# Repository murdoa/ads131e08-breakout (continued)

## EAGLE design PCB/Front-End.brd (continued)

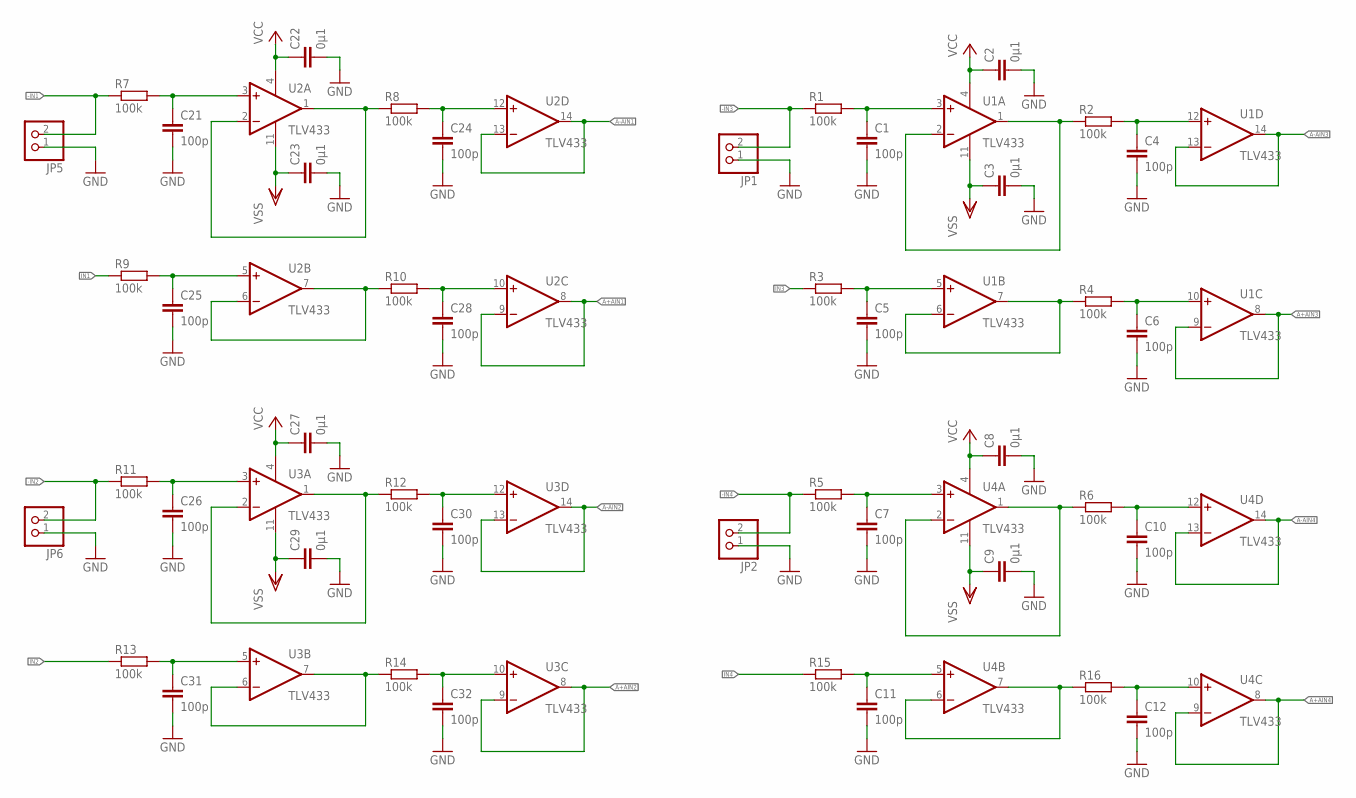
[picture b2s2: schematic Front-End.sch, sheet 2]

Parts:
C1, C4, C5, C6, C7, C10, C11, C12, C21, C24, C25, C26, C28, C30, C31, C32: 100p; C0603
C2, C3, C8, C9, C22, C23, C27, C29: 0µ1; C0603
JP1, JP2, JP5, JP6: PINHD-1X2; 1X02
R1, R2, R3, R4, R5, R6, R7, R8, R9, R10, R11, R12, R13, R14, R15, R16: 100k; R0603
U1, U2, U3, U4: TLV433; TSSOP14

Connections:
-IN1: JP5.2, R7.1
-IN2: JP6.2, R11.1
-IN3: JP1.2, R1.1
-IN4: JP2.2, R5.1
-PAS1: C21.1, R7.2, U2.3 (+IN); also elsewhere on the board
-PAS2: C26.1, R11.2, U3.3 (+IN); also elsewhere on the board
-PAS3: C1.1, R1.2, U1.3 (+IN); also elsewhere on the board
-PAS4: C7.1, R5.2, U4.3 (+IN); also elsewhere on the board
A+AIN1: U2.8 (OUT), U2.9 (-IN); also elsewhere on the board
A+AIN2: U3.8 (OUT), U3.9 (-IN); also elsewhere on the board
A+AIN3: U1.8 (OUT), U1.9 (-IN); also elsewhere on the board
A+AIN4: U4.8 (OUT), U4.9 (-IN); also elsewhere on the board
A-AIN1: U2.13 (-IN), U2.14 (OUT); also elsewhere on the board
A-AIN2: U3.13 (-IN), U3.14 (OUT); also elsewhere on the board
A-AIN3: U1.13 (-IN), U1.14 (OUT); also elsewhere on the board
A-AIN4: U4.13 (-IN), U4.14 (OUT); also elsewhere on the board
GND: C1.2, C2.2, C3.2, C4.2, C5.2, C6.2, C7.2, C8.2, C9.2, C10.2, C11.2, C12.2, C21.2, C22.2, C23.2, C24.2, C25.2, C26.2, C27.2, C28.2, C29.2, C30.2, C31.2, C32.2, JP1.1, JP2.1, JP5.1, JP6.1; also elsewhere on the board
IN1: R9.1
IN2: R13.1
IN3: R3.1
IN4: R15.1
unnamed: C4.1, R2.2, U1.12 (+IN)
unnamed: R2.1, U1.1 (OUT), U1.2 (-IN)
unnamed: C6.1, R4.2, U1.10 (+IN)
unnamed: C28.1, R10.2, U2.10 (+IN)
unnamed: C24.1, R8.2, U2.12 (+IN)
unnamed: R8.1, U2.1 (OUT), U2.2 (-IN)
unnamed: R10.1, U2.6 (-IN), U2.7 (OUT)
unnamed: R4.1, U1.6 (-IN), U1.7 (OUT)
unnamed: C30.1, R12.2, U3.12 (+IN)
unnamed: R12.1, U3.1 (OUT), U3.2 (-IN)
unnamed: C10.1, R6.2, U4.12 (+IN)
unnamed: C32.1, R14.2, U3.10 (+IN)
unnamed: R14.1, U3.6 (-IN), U3.7 (OUT)
unnamed: R6.1, U4.1 (OUT), U4.2 (-IN)
unnamed: C12.1, R16.2, U4.10 (+IN)
unnamed: R16.1, U4.6 (-IN), U4.7 (OUT)
PAS1: C5.1, C25.1, R3.2, R9.2, U1.5 (+IN), U2.5 (+IN); also elsewhere on the board
PAS2: C11.1, C31.1, R13.2, R15.2, U3.5 (+IN), U4.5 (+IN); also elsewhere on the board
VCC: C2.1, C8.1, C22.1, C27.1, U1.4 (V+), U2.4 (V+), U3.4 (V+), U4.4 (V+); also elsewhere on the board
VSS: C3.1, C9.1, C23.1, C29.1, U1.11 (V-), U2.11 (V-), U3.11 (V-), U4.11 (V-); also elsewhere on the board

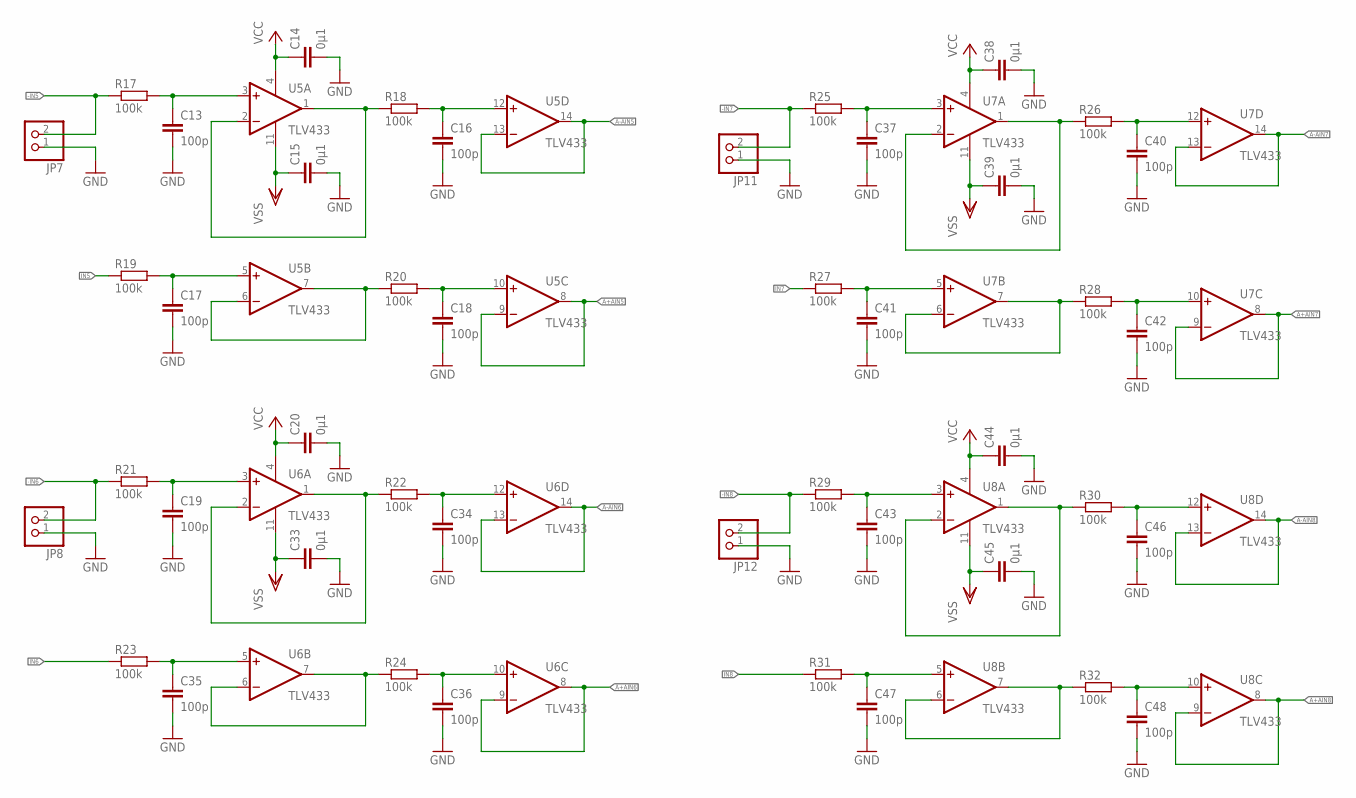
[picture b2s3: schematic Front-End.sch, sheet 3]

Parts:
C13, C16, C17, C18, C19, C34, C35, C36, C37, C40, C41, C42, C43, C46, C47, C48: 100p; C0603
C14, C15, C20, C33, C38, C39, C44, C45: 0µ1; C0603
JP7, JP8, JP11, JP12: PINHD-1X2; 1X02
R17, R18, R19, R20, R21, R22, R23, R24, R25, R26, R27, R28, R29, R30, R31, R32: 100k; R0603
U5, U6, U7, U8: TLV433; TSSOP14

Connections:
-IN5: JP7.2, R17.1
-IN6: JP8.2, R21.1
-IN7: JP11.2, R25.1
-IN8: JP12.2, R29.1
-PAS5: C13.1, R17.2, U5.3 (+IN); also elsewhere on the board
-PAS6: C19.1, R21.2, U6.3 (+IN); also elsewhere on the board
-PAS7: C37.1, R25.2, U7.3 (+IN); also elsewhere on the board
-PAS8: C43.1, R29.2, U8.3 (+IN); also elsewhere on the board
A+AIN5: U5.8 (OUT), U5.9 (-IN); also elsewhere on the board
A+AIN6: U6.8 (OUT), U6.9 (-IN); also elsewhere on the board
A+AIN7: U7.8 (OUT), U7.9 (-IN); also elsewhere on the board
A+AIN8: U8.8 (OUT), U8.9 (-IN); also elsewhere on the board
A-AIN5: U5.13 (-IN), U5.14 (OUT); also elsewhere on the board
A-AIN6: U6.13 (-IN), U6.14 (OUT); also elsewhere on the board
A-AIN7: U7.13 (-IN), U7.14 (OUT); also elsewhere on the board
A-AIN8: U8.13 (-IN), U8.14 (OUT); also elsewhere on the board
GND: C13.2, C14.2, C15.2, C16.2, C17.2, C18.2, C19.2, C20.2, C33.2, C34.2, C35.2, C36.2, C37.2, C38.2, C39.2, C40.2, C41.2, C42.2, C43.2, C44.2, C45.2, C46.2, C47.2, C48.2, JP7.1, JP8.1, JP11.1, JP12.1; also elsewhere on the board
IN5: R19.1
IN6: R23.1
IN7: R27.1
IN8: R31.1
unnamed: C16.1, R18.2, U5.12 (+IN)
unnamed: R18.1, U5.1 (OUT), U5.2 (-IN)
unnamed: C18.1, R20.2, U5.10 (+IN)
unnamed: R20.1, U5.6 (-IN), U5.7 (OUT)
unnamed: C34.1, R22.2, U6.12 (+IN)
unnamed: R22.1, U6.1 (OUT), U6.2 (-IN)
unnamed: C36.1, R24.2, U6.10 (+IN)
unnamed: R24.1, U6.6 (-IN), U6.7 (OUT)
unnamed: C40.1, R26.2, U7.12 (+IN)
unnamed: R26.1, U7.1 (OUT), U7.2 (-IN)
unnamed: C42.1, R28.2, U7.10 (+IN)
unnamed: R28.1, U7.6 (-IN), U7.7 (OUT)
unnamed: C46.1, R30.2, U8.12 (+IN)
unnamed: R30.1, U8.1 (OUT), U8.2 (-IN)
unnamed: C48.1, R32.2, U8.10 (+IN)
unnamed: R32.1, U8.6 (-IN), U8.7 (OUT)
PAS1: C17.1, C41.1, R19.2, R27.2, U5.5 (+IN), U7.5 (+IN); also elsewhere on the board
PAS2: C35.1, C47.1, R23.2, R31.2, U6.5 (+IN), U8.5 (+IN); also elsewhere on the board
VCC: C14.1, C20.1, C38.1, C44.1, U5.4 (V+), U6.4 (V+), U7.4 (V+), U8.4 (V+); also elsewhere on the board
VSS: C15.1, C33.1, C39.1, C45.1, U5.11 (V-), U6.11 (V-), U7.11 (V-), U8.11 (V-); also elsewhere on the board

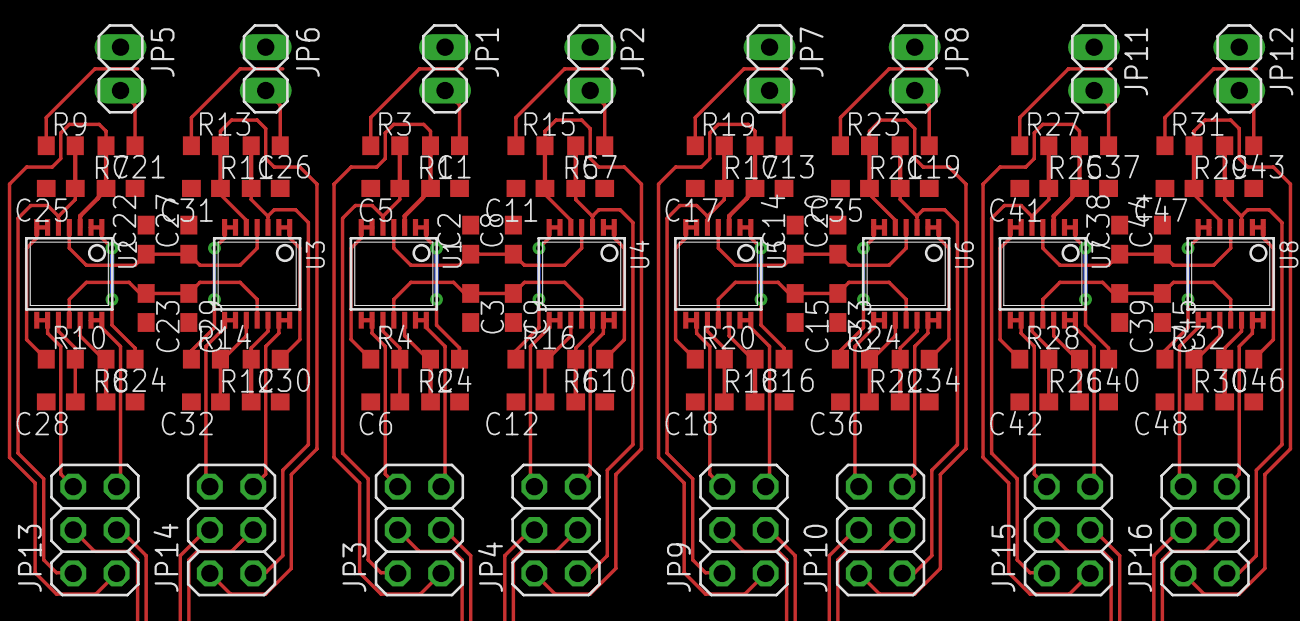
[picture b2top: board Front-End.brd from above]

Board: 2 copper layers, 104 parts (0 on the bottom side), 69 nets.

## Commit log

2018-11-30 README.md created online with Bitbucket
2018-11-30 Uploaded board files
2018-11-30 README.md edited online with Bitbucket
2018-11-30 Minor Touchups
2018-12-05 GitIgnore
2018-12-05 Cleaned
2018-12-05 Op-amp Power Routed
2018-12-05 Op-amp Power Supply Routing Finished
2018-12-19 Clean PSU
2019-11-09 Modified Board
2019-11-25 finalized board
2019-11-25 corrected merge error
2019-11-25 README.md edited
2019-11-25 Created PNG of PDFs
2019-11-25 Added silkscreen PNG
2019-11-26 Added schematic PDF
2019-12-13 Renamed Render.png to Final.png
2019-12-13 Modified Final.png
2019-12-23 Modified Blog.md
2020-01-02 Modified image size
2020-01-02 Modified silkscreen image
2020-01-02 Edited image
2021-08-14 Included Licence
